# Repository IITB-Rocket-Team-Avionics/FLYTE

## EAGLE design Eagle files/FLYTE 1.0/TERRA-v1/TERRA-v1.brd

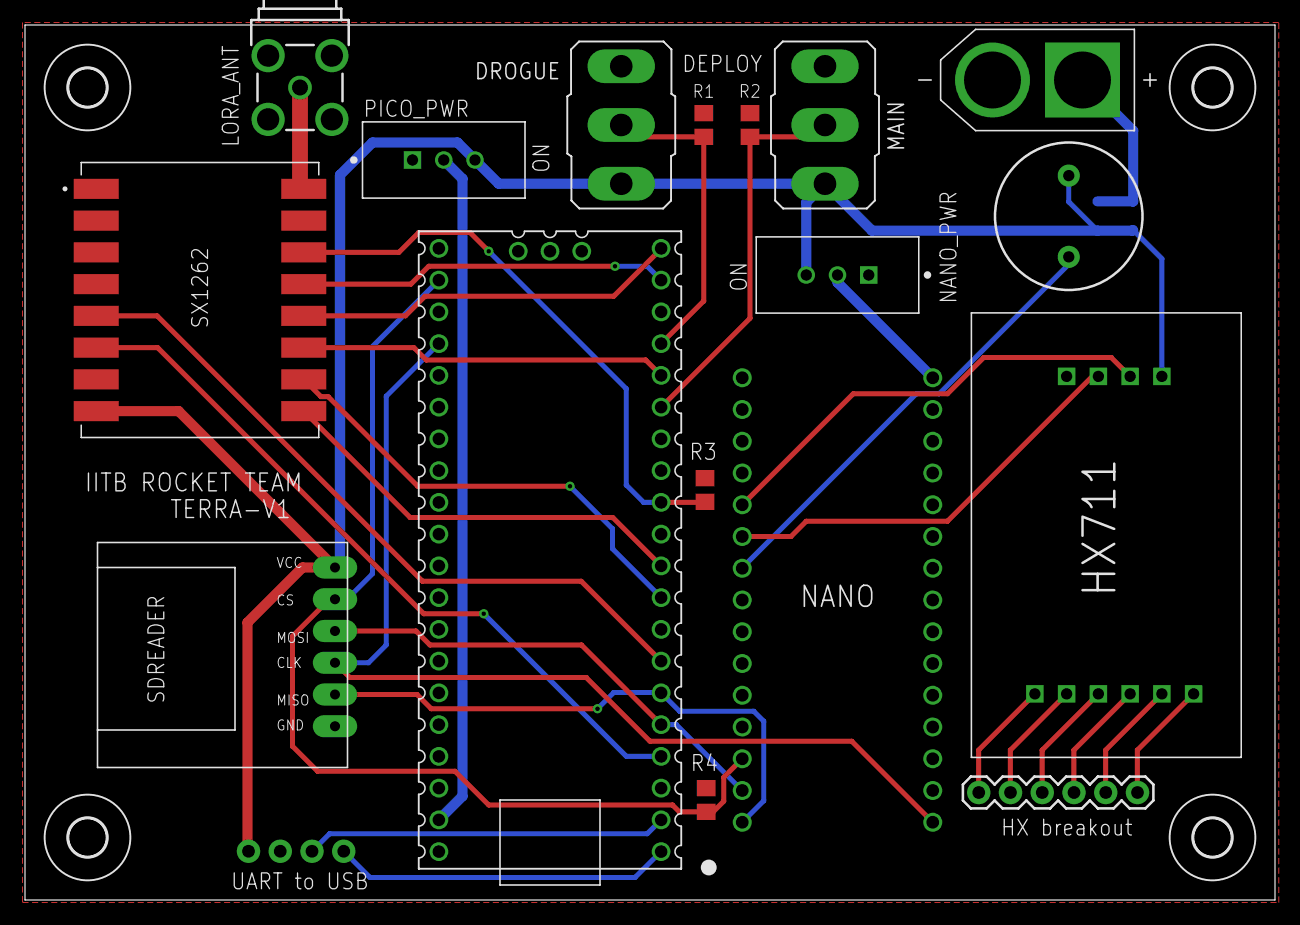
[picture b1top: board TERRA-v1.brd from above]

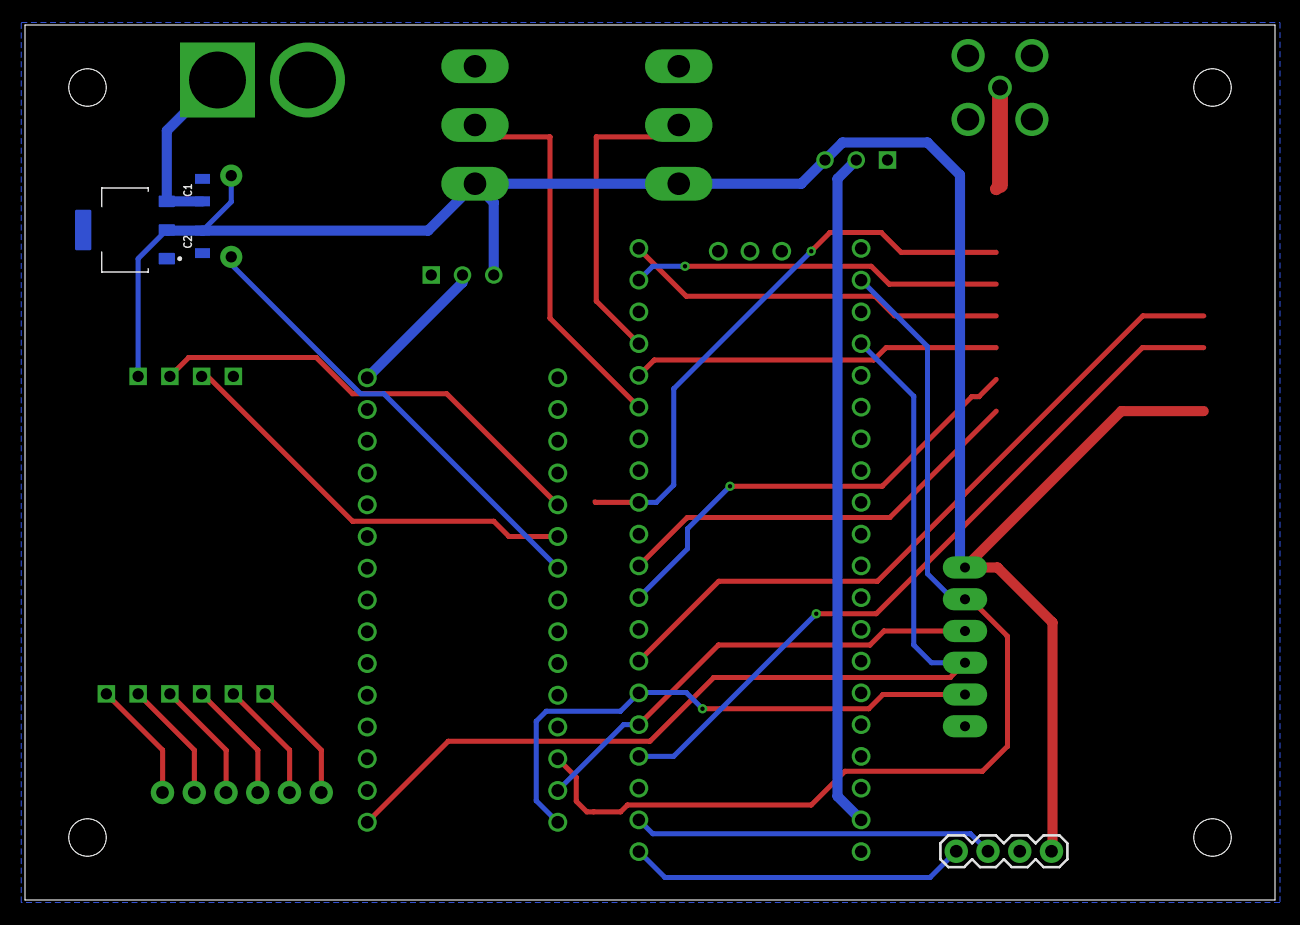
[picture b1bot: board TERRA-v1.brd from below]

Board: 2 copper layers, 100.0 x 70.0 mm, 25 parts (4 on the bottom side), 31 nets.

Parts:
C1, C2: 22uF; 0805
DROGUE: M9040P
HX711: HX711
J1: XT60-M; AMASS_XT60-M
J2: NANO_FOOTPRINT; NANO
J3: 1X04
LORA_ANT: BU-SMA-G
LS1: BUZZER-PTH; BUZZER-12MM
MAIN: M9040P
NANO_PWR: 1825159-1; SW_1825159-1
PICO_PWR: 1825159-1; SW_1825159-1
R1, R2, R3, R4: 4.7K; R0805
SV1: 1X06
SX1262: CORE1262-868M; XCVR_CORE1262-868M
U1: RASPBERRY_PICOTH; PICO-PKG-TH
U3: AMS1117-3.3; SOT229P700X180-4N
U$1: SDREADER
U$2, U$3, U$5, U$6: 3,0

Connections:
3V3: C2.2, DROGUE.1, HX711.VCC, J3.4, LS1.+, MAIN.1, NANO_PWR.3, PICO_PWR.3, SX1262.8, U3.2, U$1.VCC
BUSY: SX1262.9, U1.10
BUZZER: J2.7, LS1.-
CLK: SX1262.13, U1.19
CLK-ARD: HX711.SCK, J2.5
CS: R3.1, SX1262.14, U1.12
DATA: HX711.DT, J2.6
DIO1: SX1262.6, U1.4
DIO2: SX1262.5, U1.7
DROG: DROGUE.2, R1.1, U1.17
GND: C1.2, C2.1, DROGUE.3, HX711.GND, J1.N, J2.4, J2.29, J3.3, LORA_ANT.2, LORA_ANT.3, LORA_ANT.4, LORA_ANT.5, MAIN.3, NANO_PWR.1, PICO_PWR.1, R1.2, R2.2, R3.2, R4.2, SX1262.1, SX1262.2, SX1262.7, SX1262.15, U1.3, U1.8, U1.13, U1.18, U1.23, U1.28, U1.33, U1.38, U3.1, U$1.GND
MAIN: MAIN.2, R2.1, U1.15
MISO: SX1262.11, U1.16
MOSI: SX1262.12, U1.20
unnamed: LORA_ANT.1, SX1262.16
unnamed: HX711.B+, SV1.1
unnamed: HX711.B-, SV1.2
unnamed: HX711.A+, SV1.3
unnamed: HX711.A-, SV1.4
unnamed: HX711.E-, SV1.5
unnamed: HX711.E+, SV1.6
NANO_PWR: J2.30, NANO_PWR.2
PICO_PWR: PICO_PWR.2, U1.39
RESET: SX1262.10, U1.9
RX: J3.2, U1.2
SD_CLK: J2.16, U1.24, U$1.CLK
SD_CS: J2.13, R4.1, U1.22, U$1.CS
SD_MISO: J2.15, U1.6, U$1.MISO
SD_MOSI: J2.14, U1.5, U$1.MOSI
TX: J3.1, U1.1
VCC: C1.1, J1.P, U3.3

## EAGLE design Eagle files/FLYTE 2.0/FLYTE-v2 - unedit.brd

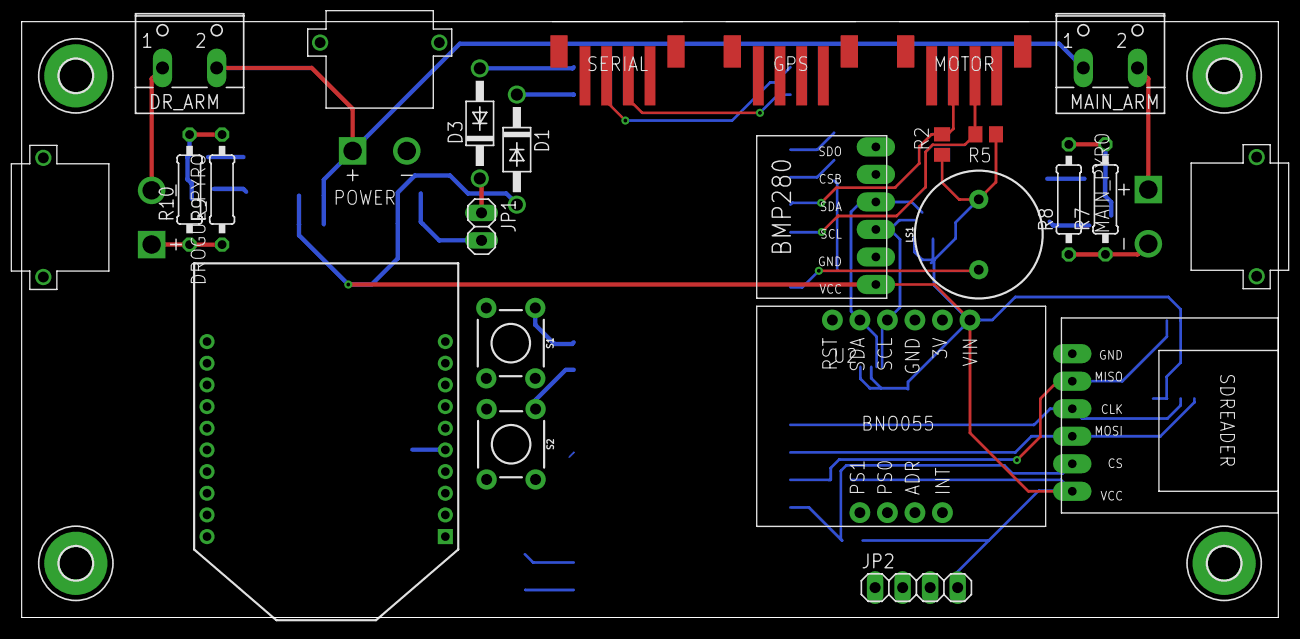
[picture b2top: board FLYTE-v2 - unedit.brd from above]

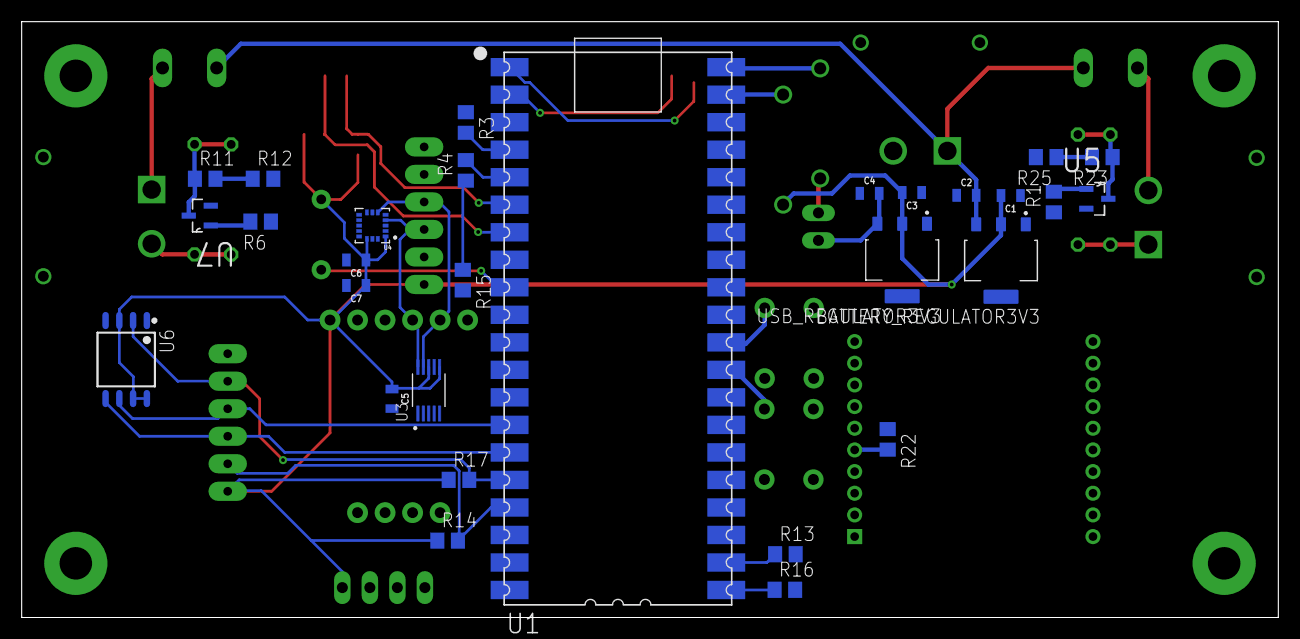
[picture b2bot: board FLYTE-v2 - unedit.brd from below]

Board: 2 copper layers, 116.0 x 55.0 mm, 58 parts (29 on the bottom side), 42 nets.

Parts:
BATTERY_REGULATOR3V3: AMS1117-3.3; SOT229P700X180-4N
C1, C2, C3, C4: 22uF; 0805
C5: 0.1uF; 0805
C6: 10 uF; 0805
C7: 100 nF; 0805
D1, D3: 1N4004; DO41-10
DROGUE_PYRO: XT30PW-M; AMASS_XT30PW-M
DR_ARM: W237-102
GPS: 4392
H1, H2, H3, H4: MOUNT-PAD-ROUND3.0; 3,0-PAD
JP1: 1X02
JP2: 1X04
LS1: BUZZER-PTH; BUZZER-12MM
MAIN_ARM: W237-102
MAIN_PYRO: XT30PW-M; AMASS_XT30PW-M
MOTOR: 4392
POWER: XT30PW-M; AMASS_XT30PW-M
R1, R6: 4.7K; R0805
R2, R3, R4, R5, R13, R14, R15, R22: 4.7K ohm; R0805
R7, R8, R9, R10: 10 ohm; 0207/10
R11, R12, R16, R17, R23, R25: 100K ohm; R0805
S1, S2: MOMENTARY-SWITCH-SPST-PTH-6.0MM; TACTILE_SWITCH_PTH_6.0MM
SERIAL: 4392
U1: PICO-PKG-NO_DEBUG
U2: XBP9B-XCST-021; DIP2200W51P200L3294H279Q20P
U3: ADS1115IDGSR; SOP50P490X110-10N
U4: H3LIS200DLTR; PQFN50P300X300X100-16N
U5, U7: BS170F; SOT91P240X120-3N
U6: W25Q32JVSSIQ; SOIC127P790X216-8N
U$1: BMP280
U$3: SDREADER
U$4: BNO055
USB_REGULATOR3V3: AMS1117-3.3; SOT229P700X180-4N

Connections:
3V3: BATTERY_REGULATOR3V3.2, C1.2, C3.2, C5.1, C6.1, C7.1, D1.A, GPS.4, JP2.4, LS1.+, R2.1, R3.1, R4.1, R5.1, R13.2, R14.1, R15.1, R16.2, R17.1, R22.1, SERIAL.4, U2.1, U3.6, U3.8, U4.1, U4.14, U4.15, U6.3, U6.7, U6.8, U$1.VCC, U$3.VCC, U$4.VIN, USB_REGULATOR3V3.2
AIR_DATA: JP2.3, U1.P$34
AIR_SCK: JP2.2, U1.P$32
ATTN: U1.P$27, U2.19
BNO_INT: U1.P$19, U$4.INT
BUZZER: LS1.-, U1.P$9
CS_FLASH: R15.2, U1.P$10, U6.1
CS_SD: R14.2, U1.P$17, U$3.CS
CS_SX: R13.1, U1.P$22, U2.17
DROGUE: R1.2, U1.P$20, U5.1
GND: BATTERY_REGULATOR3V3.1, C1.1, C2.1, C3.1, C4.1, C5.2, C6.2, C7.2, GPS.3, GPS.MP1, GPS.MP2, H1.B3,0, H2.B3,0, H3.B3,0, H4.B3,0, JP2.1, MOTOR.1, MOTOR.MP1, MOTOR.MP2, POWER.N, R1.1, R6.1, R12.2, R25.2, S1.3, S2.3, SERIAL.1, SERIAL.MP1, SERIAL.MP2, U1.P$3, U1.P$8, U1.P$13, U1.P$18, U1.P$23, U1.P$28, U1.P$33, U1.P$38, U2.10, U3.1, U3.3, U4.5, U4.7, U4.10, U4.12, U4.13, U4.16, U5.2, U6.4, U7.2, U$1.GND, U$1.SDO, U$3.GND, U$4.ADR, U$4.GND, U$4.RST, USB_REGULATOR3V3.1
MAIN: R6.2, U1.P$26, U7.1
MISO0: R16.1, U1.P$21, U2.4
MISO1: R17.2, U1.P$16, U6.2, U$3.MISO
MOSI0: U1.P$25, U2.11
MOSI1: U1.P$15, U6.5, U$3.MOSI
unnamed: D1.C, U1.P$39
unnamed: DROGUE_PYRO.N, DR_ARM.1
unnamed: S2.1, U1.P$29
unnamed: MAIN_PYRO.N, R7.1, R8.1
unnamed: R7.2, R8.2, R11.1, U7.3
unnamed: MAIN_ARM.2, MAIN_PYRO.P
unnamed: DROGUE_PYRO.P, R9.1, R10.1
unnamed: S1.1, U1.P$30
unnamed: R9.2, R10.2, R23.1, U5.3
unnamed: D3.A, U1.P$40
RX: GPS.1, U1.P$12
SCK0: U1.P$24, U2.18
SCK1: U1.P$14, U6.6, U$3.CLK
SCL0: MOTOR.3, R5.2, U1.P$7
SCL1: R4.2, U1.P$5, U3.10, U4.4, U$1.SCL, U$4.SCL
SDA0: MOTOR.2, R2.2, U1.P$6
SDA1: R3.2, U1.P$4, U3.9, U4.6, U$1.SDA, U$4.SDA
SENSE_DROG: R23.2, R25.1, U3.5
SENSE_MAIN: R11.2, R12.1, U3.4
SER_RX: SERIAL.3, U1.P$2
SER_TX: SERIAL.2, U1.P$1
SX_RESET: R22.2, U1.P$31, U2.5
TX: GPS.2, U1.P$11
VBUS: D3.C, JP1.1
VBUS_REG: C4.2, JP1.2, USB_REGULATOR3V3.3
VCC: BATTERY_REGULATOR3V3.3, C2.2, DR_ARM.2, MAIN_ARM.1, POWER.P, U3.7

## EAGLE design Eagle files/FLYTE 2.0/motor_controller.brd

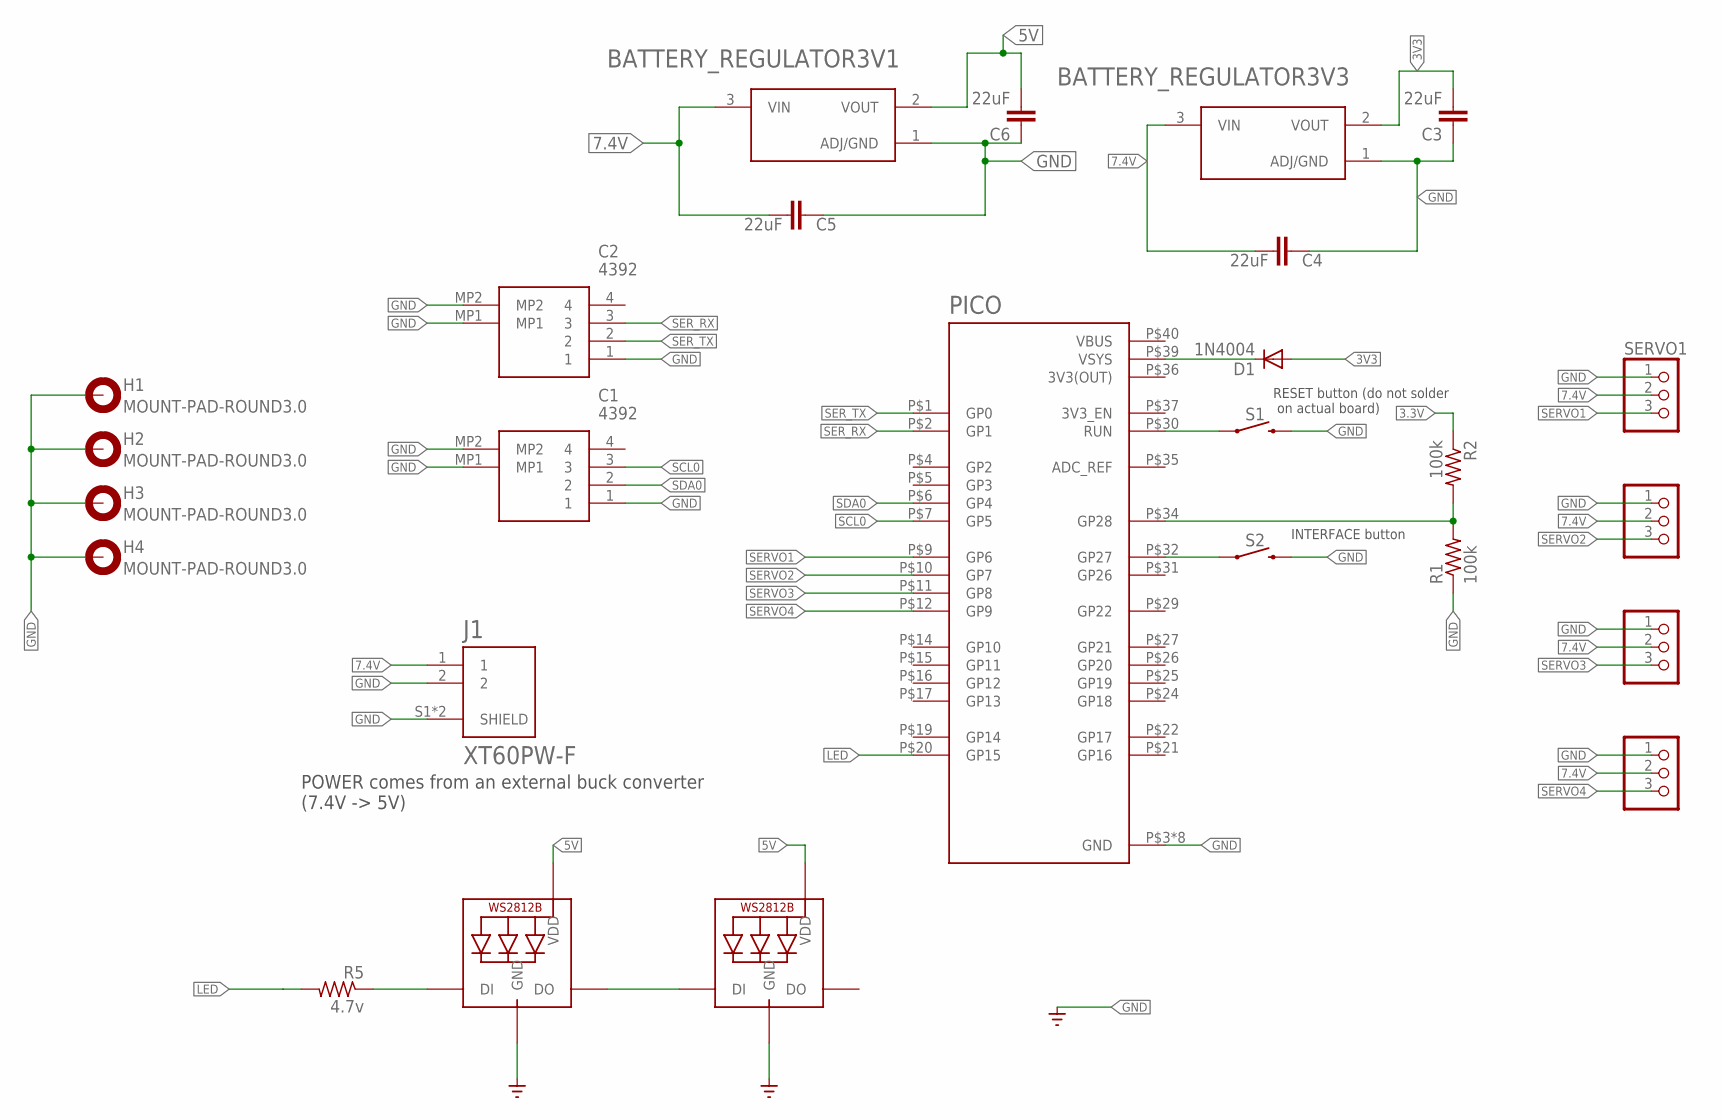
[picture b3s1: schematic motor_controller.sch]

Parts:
BATTERY_REGULATOR3V1, BATTERY_REGULATOR3V3: AMS1117-3.3; SOT229P700X180-4N
C1, C2: 4392
C3, C4, C5, C6: 22uF; 0805
D1: 1N4004; DO41-10
H1, H2, H3, H4: MOUNT-PAD-ROUND3.0; 3,0-PAD
J1: XT60PW-F; AMASS_XT60PW-F
LED1, LED2: WS2812B3535; LED3535
PICO: RASPBERRY_PICO-NO_DEBUG; PICO-PKG-NO_DEBUG
R1, R2: 100k; R0805
R5: 4.7v; R0805
S1, S2: MOMENTARY-SWITCH-SPST-PTH-6.0MM; TACTILE_SWITCH_PTH_6.0MM
SERVO1, SERVO2, SERVO3, SERVO4: PINHD-1X3; 1X03

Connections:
3.3V: R2.1
3V3: BATTERY_REGULATOR3V3.2 (VOUT), C3.2, D1.A
3V3(OUT): PICO.P$36 (3V3(OUT))
5V: BATTERY_REGULATOR3V1.2 (VOUT), C6.2, LED1.2 (VDD), LED2.2 (VDD)
7.4V: BATTERY_REGULATOR3V1.3 (VIN), BATTERY_REGULATOR3V3.3 (VIN), C4.2, C5.2, J1.1, SERVO1.2, SERVO2.2, SERVO3.2, SERVO4.2
GND: BATTERY_REGULATOR3V1.1 (ADJ/GND), BATTERY_REGULATOR3V3.1 (ADJ/GND), C1.1, C1.MP1, C1.MP2, C2.1, C2.MP1, C2.MP2, C3.1, C4.1, C5.1, C6.1, H1.B3,0, H2.B3,0, H3.B3,0, H4.B3,0, J1.2, J1.S1 (SHIELD), J1.S2 (SHIELD), LED1.4 (GND), LED2.4 (GND), PICO.P$3 (GND), PICO.P$8 (GND), PICO.P$13 (GND), PICO.P$18 (GND), PICO.P$23 (GND), PICO.P$28 (GND), PICO.P$33 (GND), PICO.P$38 (GND), R1.1, S1.3 (2), S2.3 (2), SERVO1.1, SERVO2.1, SERVO3.1, SERVO4.1
LED: PICO.P$20 (GP15), R5.2
unnamed: D1.C, PICO.P$39 (VSYS)
unnamed: PICO.P$30 (RUN), S1.1
unnamed: PICO.P$32 (GP27), S2.1
unnamed: PICO.P$34 (GP28), R1.2, R2.2
unnamed: LED1.3 (DO), LED2.1 (DI)
unnamed: LED1.1 (DI), R5.1
SCL0: C1.3, PICO.P$7 (GP5)
SDA0: C1.2, PICO.P$6 (GP4)
SERVO1: PICO.P$9 (GP6), SERVO1.3
SERVO2: PICO.P$10 (GP7), SERVO2.3
SERVO3: PICO.P$11 (GP8), SERVO3.3
SERVO4: PICO.P$12 (GP9), SERVO4.3
SER_RX: C2.3, PICO.P$2 (GP1)
SER_TX: C2.2, PICO.P$1 (GP0)
VBUS: PICO.P$40 (VBUS)

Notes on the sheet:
RESET button (do not solder on actual board)
INTERFACE button
POWER comes from an external buck converter (7.4V -> 5V)

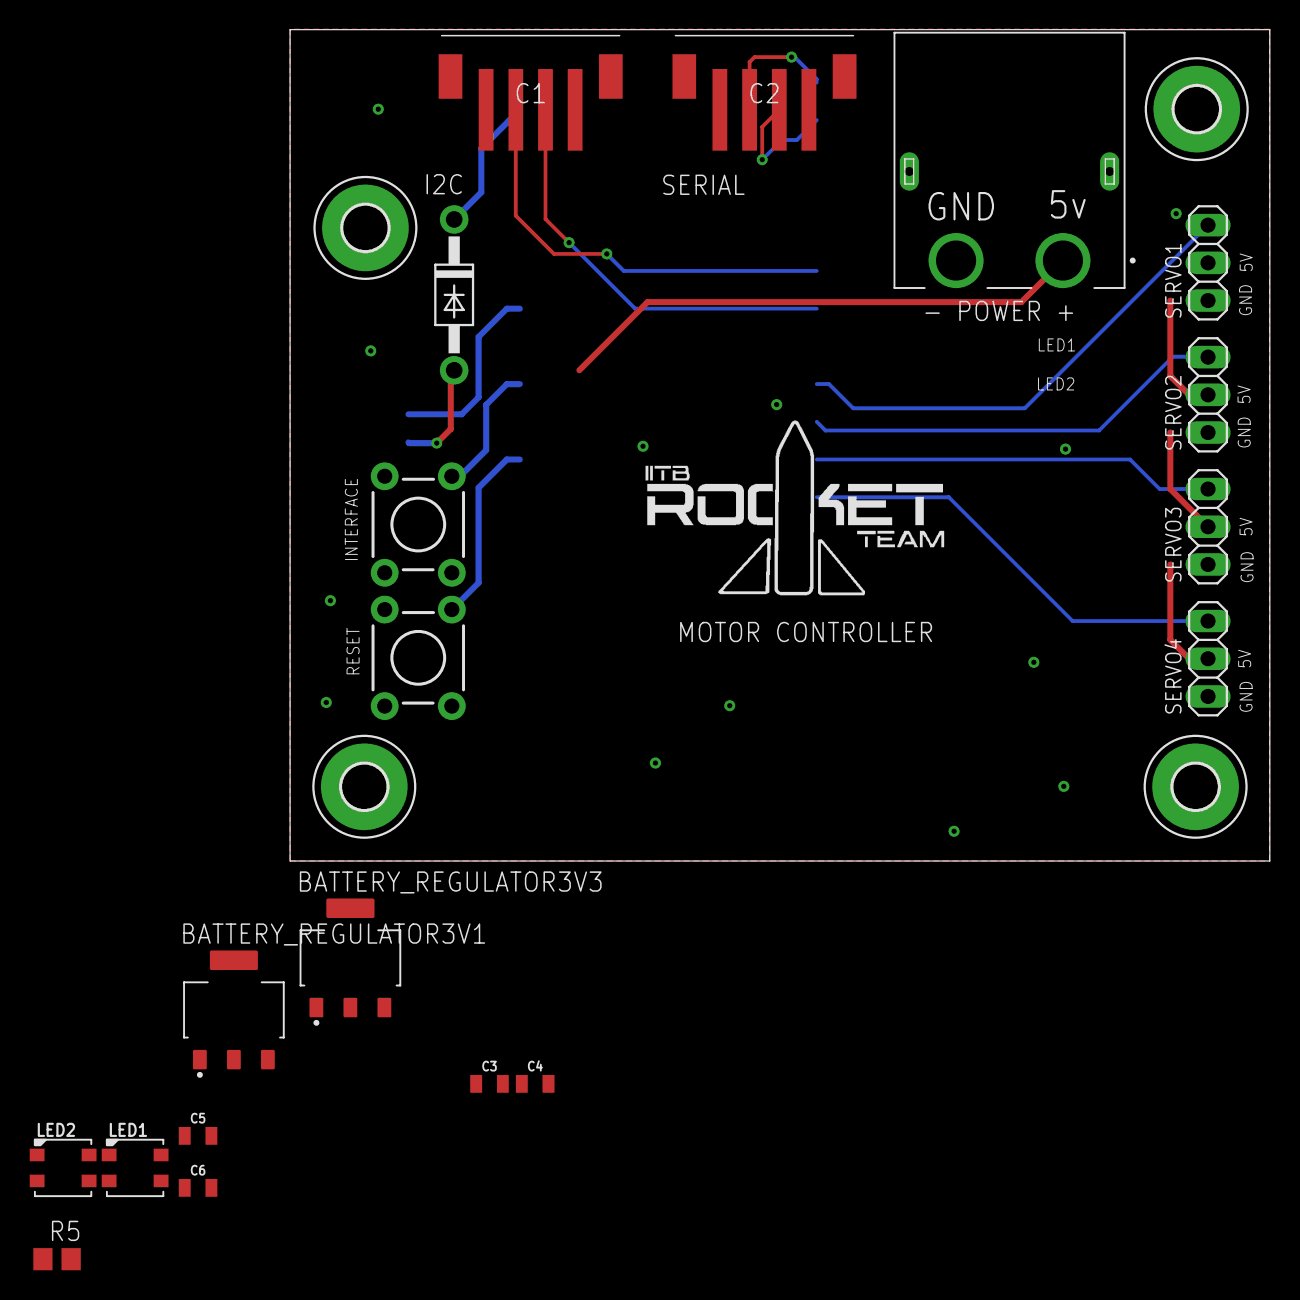
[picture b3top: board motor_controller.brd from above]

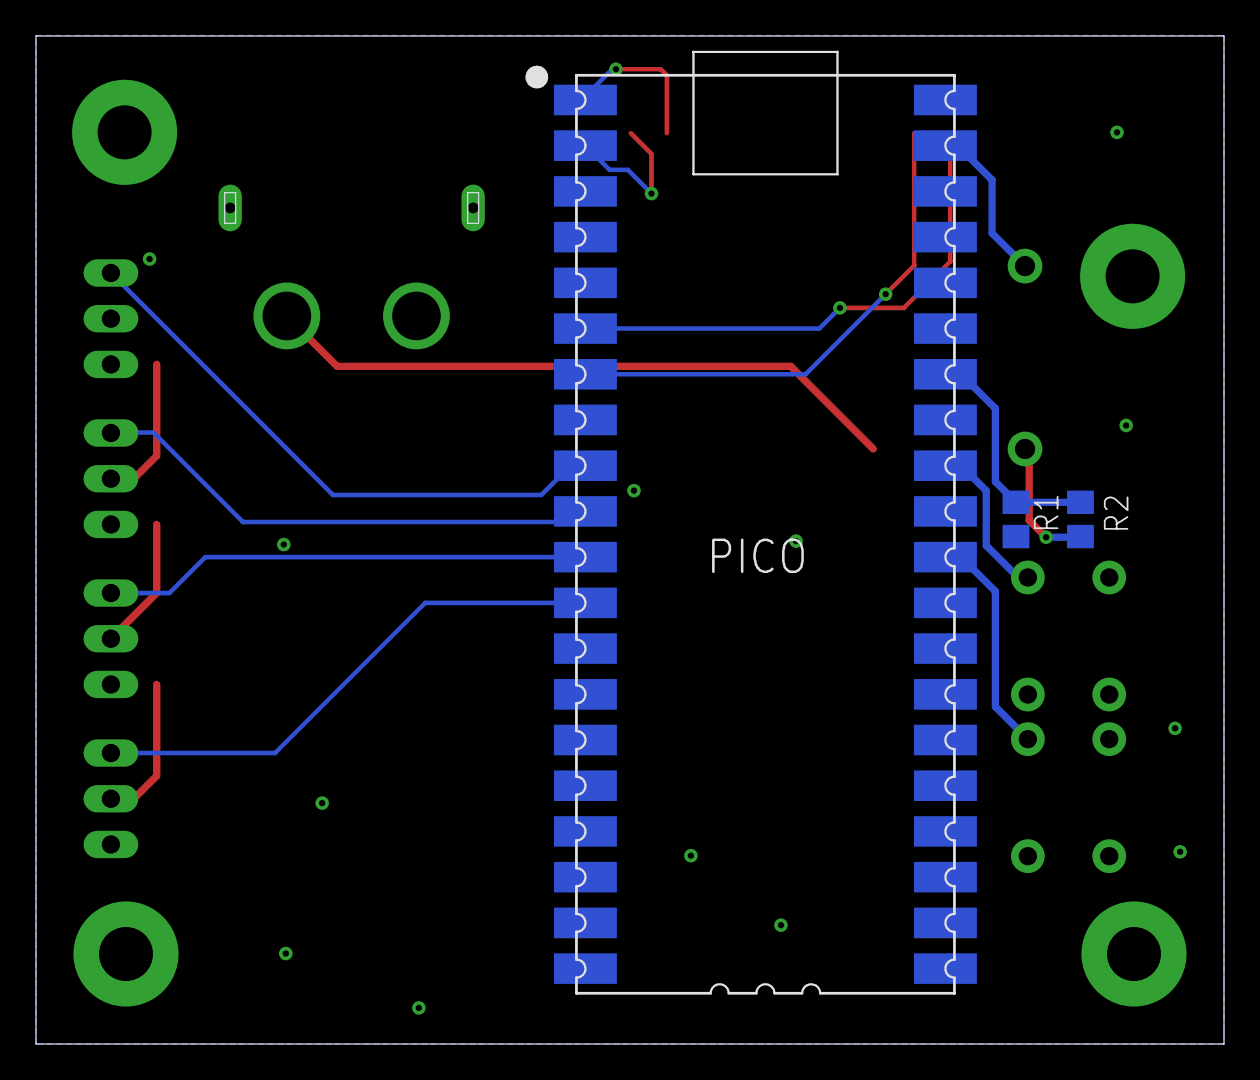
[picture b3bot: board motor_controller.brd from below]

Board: 2 copper layers, 66.0 x 56.0 mm, 26 parts (3 on the bottom side), 19 nets.

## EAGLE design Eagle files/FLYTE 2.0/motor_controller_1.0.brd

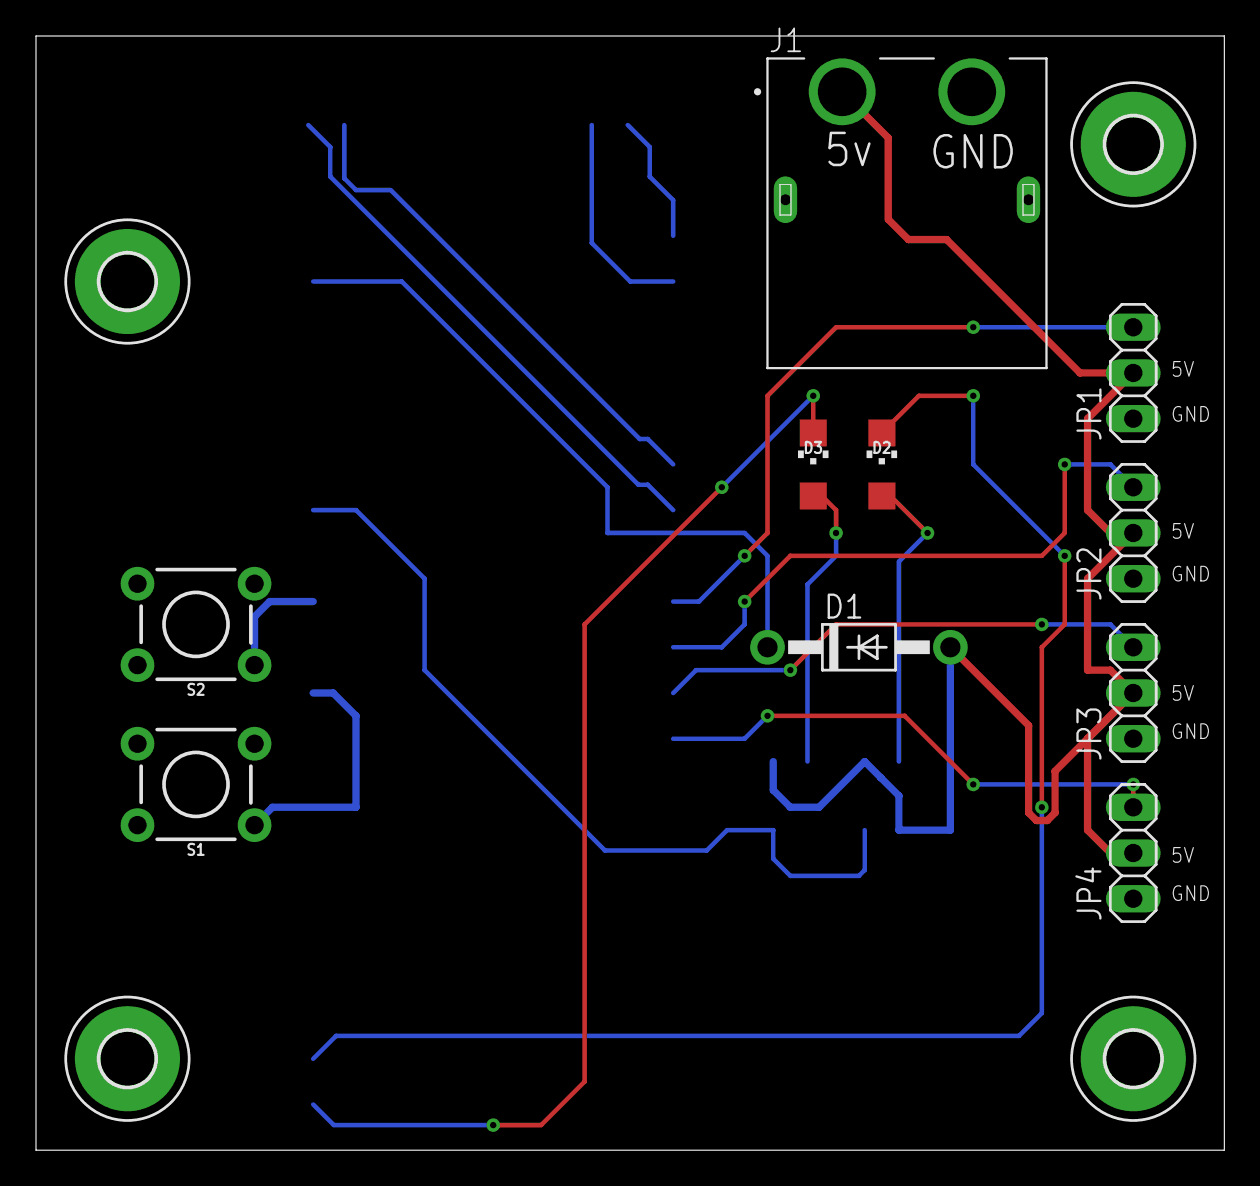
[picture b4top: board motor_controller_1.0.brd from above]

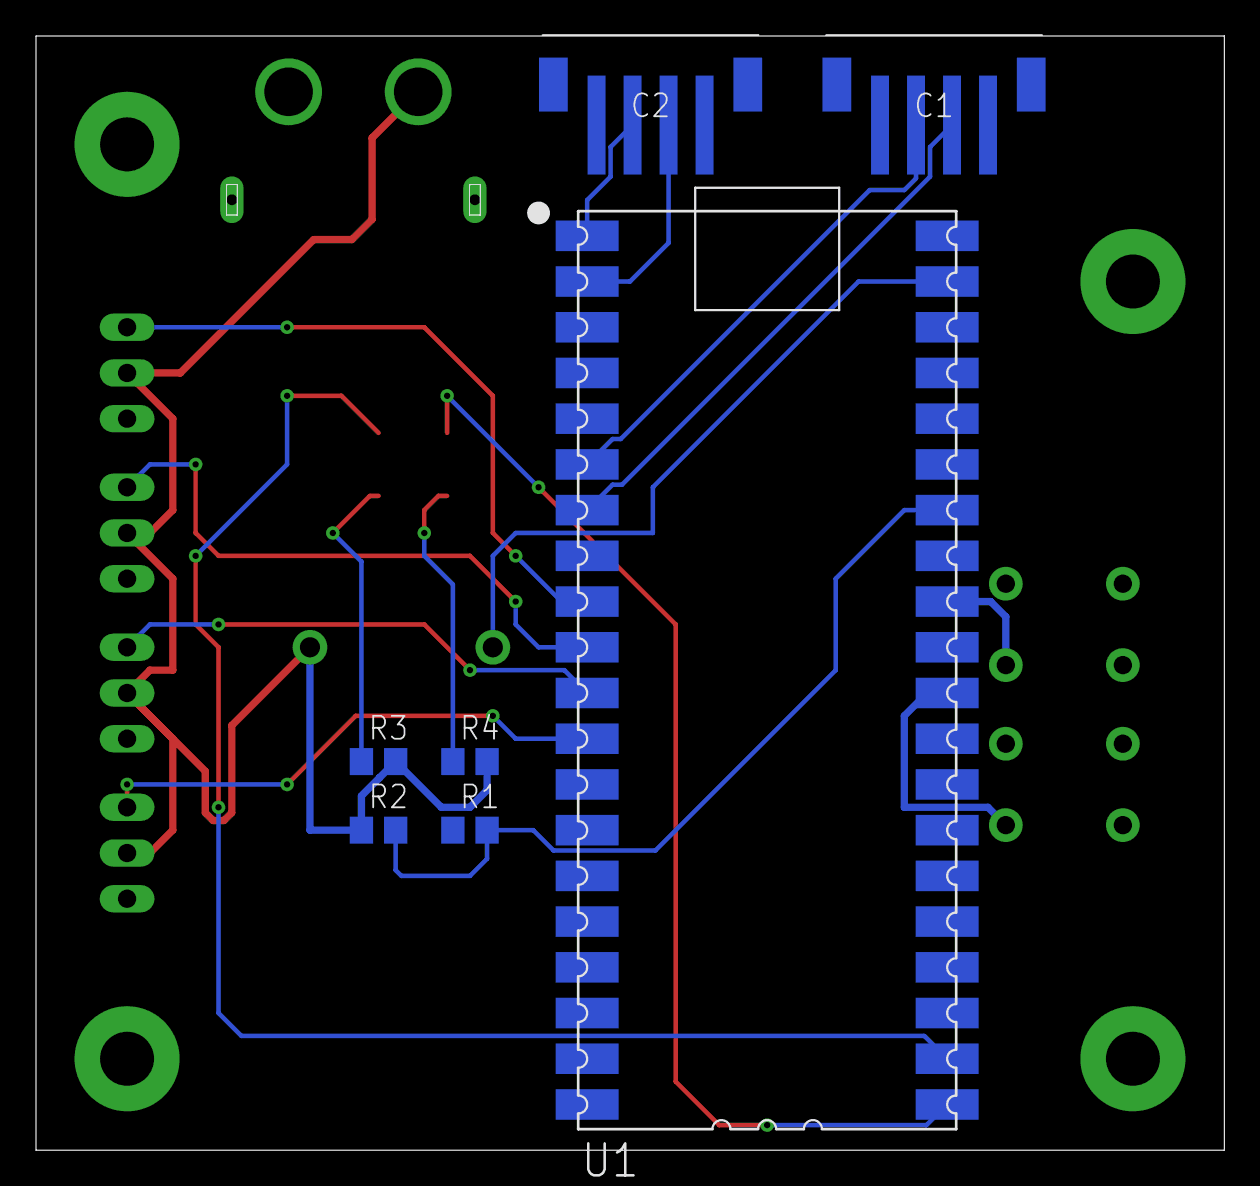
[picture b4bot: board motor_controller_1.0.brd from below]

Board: 2 copper layers, 66.0 x 61.9 mm, 21 parts (7 on the bottom side), 18 nets.

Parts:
C1, C2: 4392
D1: 1N4004; DO41-10
D2, D3: CHIPLED_1206
H1, H2, H3, H4: MOUNT-PAD-ROUND3.0; 3,0-PAD
J1: XT60PW-F; AMASS_XT60PW-F
JP1, JP2, JP3, JP4: 1X03
R1, R2: 100k; R0805
R3, R4: R0805
S1, S2: MOMENTARY-SWITCH-SPST-PTH-6.0MM; TACTILE_SWITCH_PTH_6.0MM
U1: PICO-PKG-NO_DEBUG

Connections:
5V: D1.A, J1.1, JP1.2, JP2.2, JP3.2, JP4.2, R2.1, R3.2, R4.2
GND: C1.1, C1.MP1, C1.MP2, C2.1, C2.MP1, C2.MP2, H1.B3,0, H2.B3,0, H3.B3,0, H4.B3,0, J1.2, J1.S1, J1.S2, JP1.1, JP2.1, JP3.1, JP4.1, R1.1, S1.3, S2.3, U1.P$3, U1.P$8, U1.P$13, U1.P$18, U1.P$23, U1.P$28, U1.P$33, U1.P$38
unnamed: D1.C, U1.P$39
unnamed: S1.1, U1.P$30
unnamed: S2.1, U1.P$32
unnamed: R1.2, R2.2, U1.P$34
unnamed: D2.C, U1.P$22
unnamed: D3.C, U1.P$21
unnamed: D2.A, R3.1
unnamed: D3.A, R4.1
SCL0: C1.3, U1.P$7
SDA0: C1.2, U1.P$6
SERVO1: JP1.3, U1.P$9
SERVO2: JP2.3, U1.P$10
SERVO3: JP3.3, U1.P$11
SERVO4: JP4.3, U1.P$12
SER_RX: C2.3, U1.P$2
SER_TX: C2.2, U1.P$1

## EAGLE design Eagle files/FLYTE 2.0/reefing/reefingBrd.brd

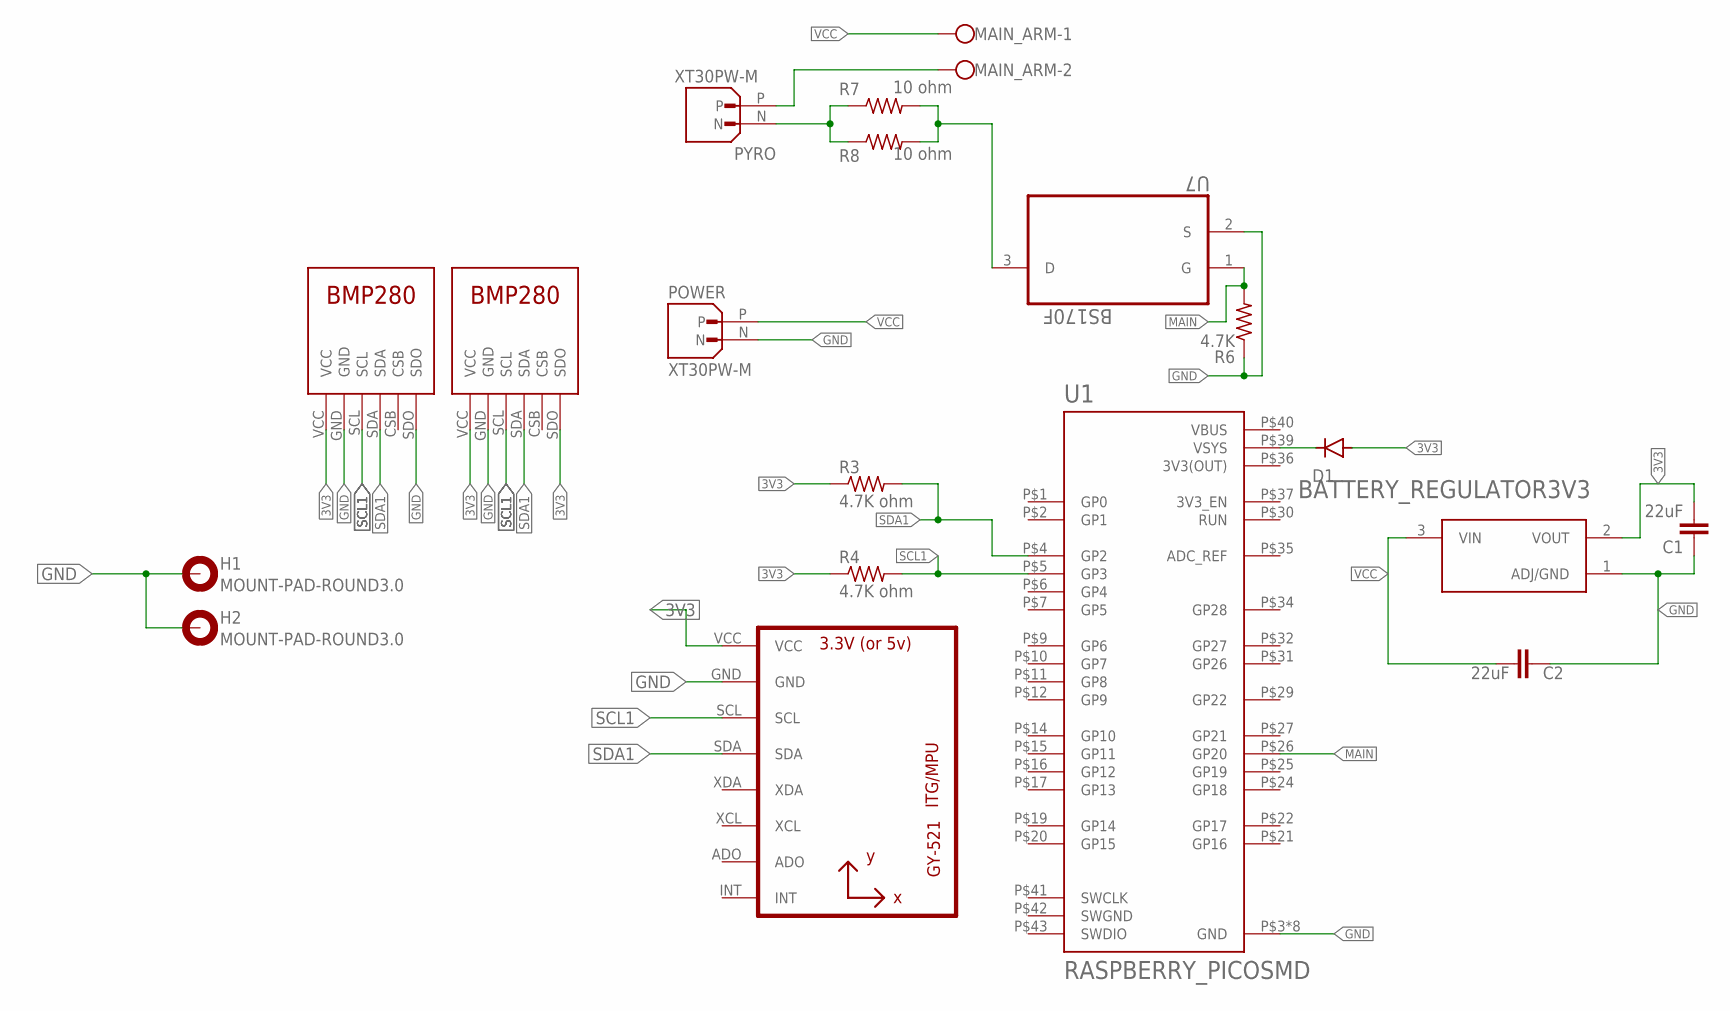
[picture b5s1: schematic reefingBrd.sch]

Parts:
BATTERY_REGULATOR3V3: AMS1117-3.3; SOT229P700X180-4N
C1, C2: 22uF; 0805
D1: 1N4004; DO41-10
H1, H2: MOUNT-PAD-ROUND3.0; 3,0-PAD
MAIN_ARM: W237-102
POWER: XT30PW-M; AMASS_XT30PW-M
PYRO: XT30PW-M; AMASS_XT30PW-M
R3, R4: 4.7K ohm; R0805
R6: 4.7K; R0805
R7, R8: 10 ohm; 0207/10
U1: RASPBERRY_PICOSMD; PICO-PKG-SMD
U2: GY-521MPU6050; GY-521
U7: BS170F; SOT91P240X120-3N
U$1, U$2: BMP280

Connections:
3V3: BATTERY_REGULATOR3V3.2 (VOUT), C1.2, D1.A, R3.1, R4.1, U2.VCC, U$1.VCC, U$2.SDO, U$2.VCC
3V3(OUT): U1.P$36 (3V3(OUT))
GND: BATTERY_REGULATOR3V3.1 (ADJ/GND), C1.1, C2.1, H1.B3,0, H2.B3,0, POWER.N, R6.1, U1.P$3 (GND), U1.P$8 (GND), U1.P$13 (GND), U1.P$18 (GND), U1.P$23 (GND), U1.P$28 (GND), U1.P$33 (GND), U1.P$38 (GND), U2.GND, U7.2 (S), U$1.GND, U$1.SDO, U$2.GND
MAIN: R6.2, U1.P$26 (GP20), U7.1 (G)
unnamed: D1.C, U1.P$39 (VSYS)
unnamed: PYRO.N, R7.1, R8.1
unnamed: R7.2, R8.2, U7.3 (D)
unnamed: MAIN_ARM.2, PYRO.P
SCL1: R4.2, U1.P$5 (GP3), U2.SCL, U$1.SCL, U$2.SCL
SDA1: R3.2, U1.P$4 (GP2), U2.SDA, U$1.SDA, U$2.SDA
SWGND: U1.P$42 (SWGND)
VBUS: U1.P$40 (VBUS)
VCC: BATTERY_REGULATOR3V3.3 (VIN), C2.2, MAIN_ARM.1, POWER.P

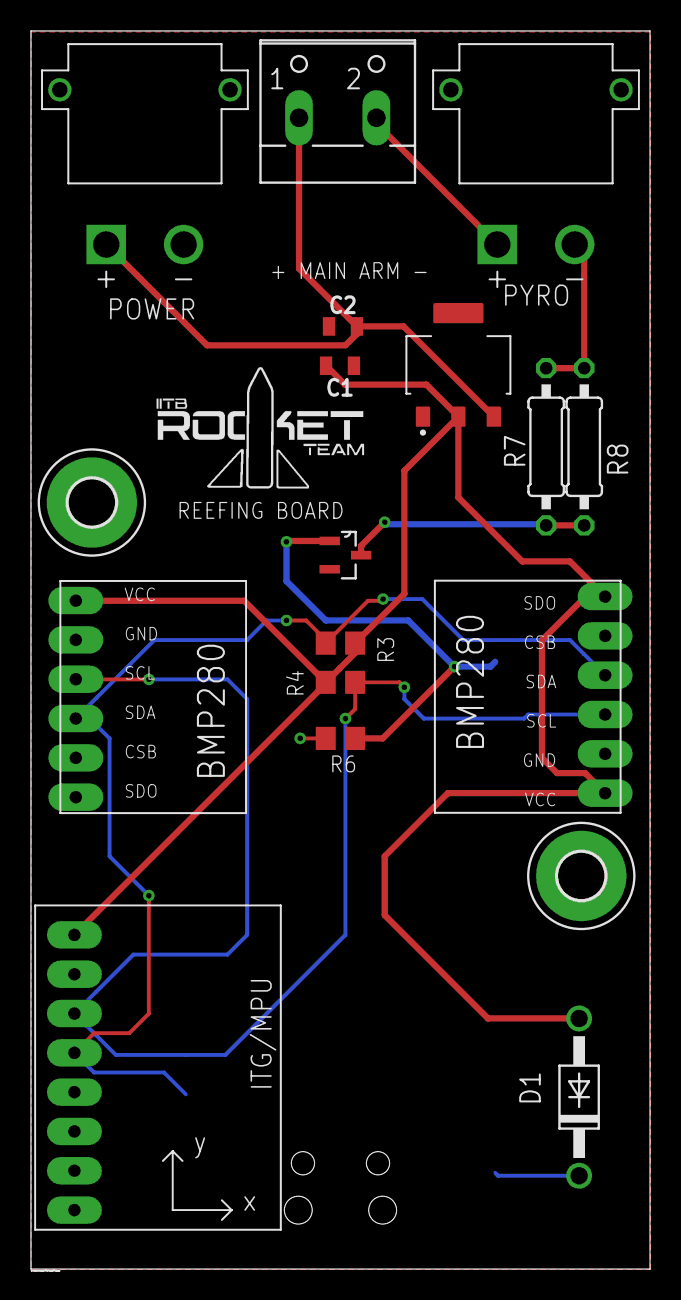
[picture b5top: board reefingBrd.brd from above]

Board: 2 copper layers, 40.0 x 80.0 mm, 19 parts (1 on the bottom side), 10 nets.

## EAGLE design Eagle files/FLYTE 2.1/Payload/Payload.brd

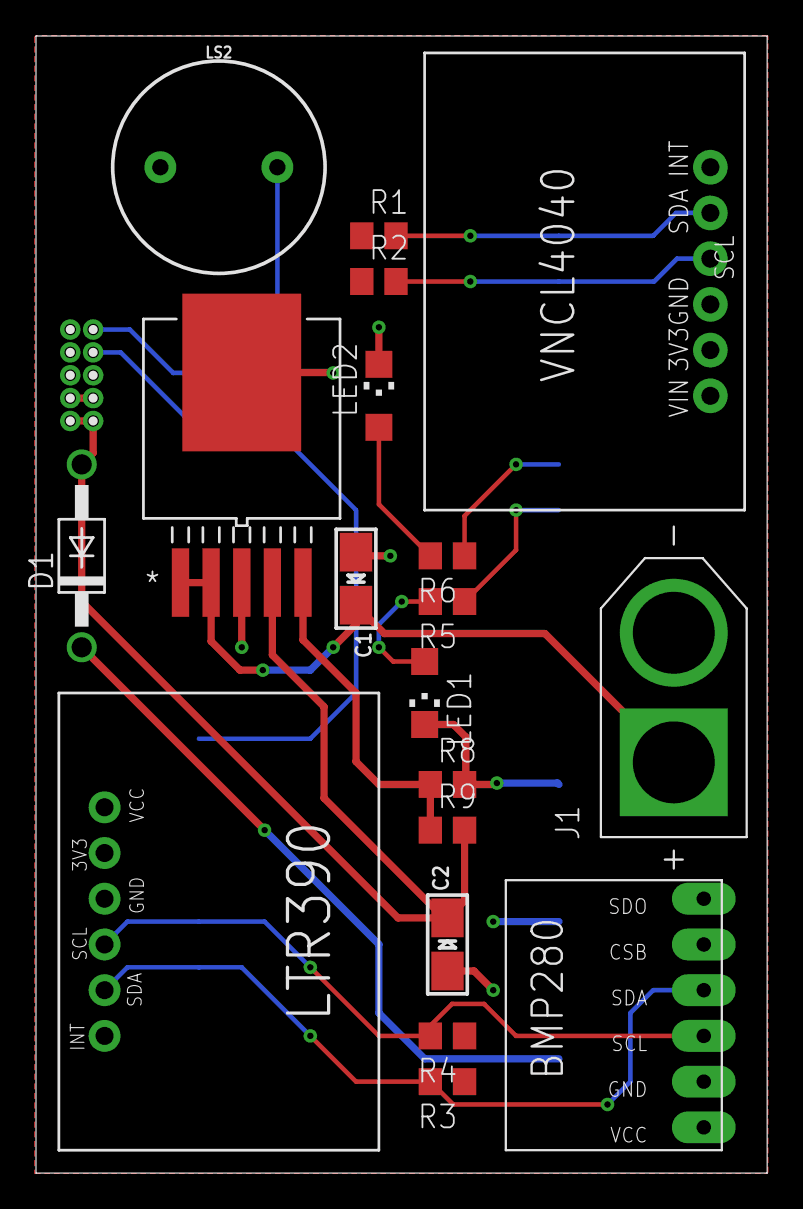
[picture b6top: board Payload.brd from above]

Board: 2 copper layers, 40.6 x 63.2 mm, 22 parts (1 on the bottom side), 17 nets.

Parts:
C1, C2: 10 uF; EIA3216-18/A-W
D1: 1N4004; DO41-10
J1: XT60-M; AMASS_XT60-M
LED1, LED2: CHIPLED_1206
LS2: BUZZER-PTH; BUZZER-12MM
R1, R2, R3, R4: 4.7K ohm; R0805
R5, R6: 330 ohm; R0805
R8: 100k ohm; R0805
R9: 301k ohm; R0805
U1: PICO-PKG-NO_DEBUG
U2: MIC29302WU-TRTO-263-5_MCH-M; TO-263-5_MCH-M
U$1: VCNL4040
U$3: BMP280
U$4: LTR390
U$5, U$6: 1X5

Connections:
3V3: R1.1, R2.1, R3.1, R4.1, U1.P$36, U$1.VIN, U$3.VCC, U$4.VCC
5V: C2.+, D1.A, R9.2, U2.4, U$5.5, U$6.1
7.4V: C1.+, J1.P, U2.1, U2.2
BUZZER: LS2.+, U1.P$9
GND: C1.-, C2.-, J1.N, LED1.C, LED2.C, LS2.-, R8.2, U1.P$3, U1.P$8, U1.P$13, U1.P$18, U1.P$23, U1.P$28, U1.P$33, U1.P$38, U2.3, U2.6, U$1.GND, U$3.GND, U$4.GND, U$5.4, U$6.2
unnamed: D1.C, U1.P$39
unnamed: R5.1, U1.P$27
unnamed: LED2.A, R6.2
unnamed: LED1.A, R5.2
unnamed: R6.1, U1.P$26
unnamed: R8.1, R9.1, U2.5
RX: U1.P$17, U$5.1
SCL0: R2.2, U1.P$22, U$1.SCL
SCL1: R4.2, U1.P$5, U$3.SCL, U$4.SCL
SDA0: R1.2, U1.P$21, U$1.SDA
SDA1: R3.2, U1.P$4, U$3.SDA, U$4.SDA
TX: U1.P$16, U$5.2

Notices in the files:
parts and their libraries:
SparkFun-Capacitors: Licensing: Creative Commons ShareAlike 4.0 International - https://creativecommons.org/licenses/by-sa/4.0
microbuilder: This work is placed in the public domain, and may be freely used for commercial and non-commercial work with the following conditions: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
